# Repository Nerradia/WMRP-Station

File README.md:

# WMRP-Station

Seeing the quality of WMRP tips from Weller, I wanted to buil my own station, cheaper that the official one.
It is still in development and some improvements are still to be made.
There is two PCBs : The first one seats in the base, and the other one is in the handle.

The first circuit has two microcontrollers, one dedicated to power regulation, and the other one for everything else. The power regulation is made with a half-bridge filtered with two LC low-pass filters. The PWM frequency is at about 100 KHz (I'm not sure, I need to check that), this way, the heating element will receive a smooth current and voltage. On an early version of this station, which was sending square-waves, it seemed to break the heating element.

The second is just made of some sensors to measure temperature of the tip, measure the acceleration of the handle (for automatic start and stop), to detect touch and finally to light up an RGB LED. These two last functions are not yet implemented, I neeed to make an other PCB.

To order the last version of PCBs :
https://pcbs.io/share/zjX5Z
https://pcbs.io/share/z5bD1

BOM is coming soon.

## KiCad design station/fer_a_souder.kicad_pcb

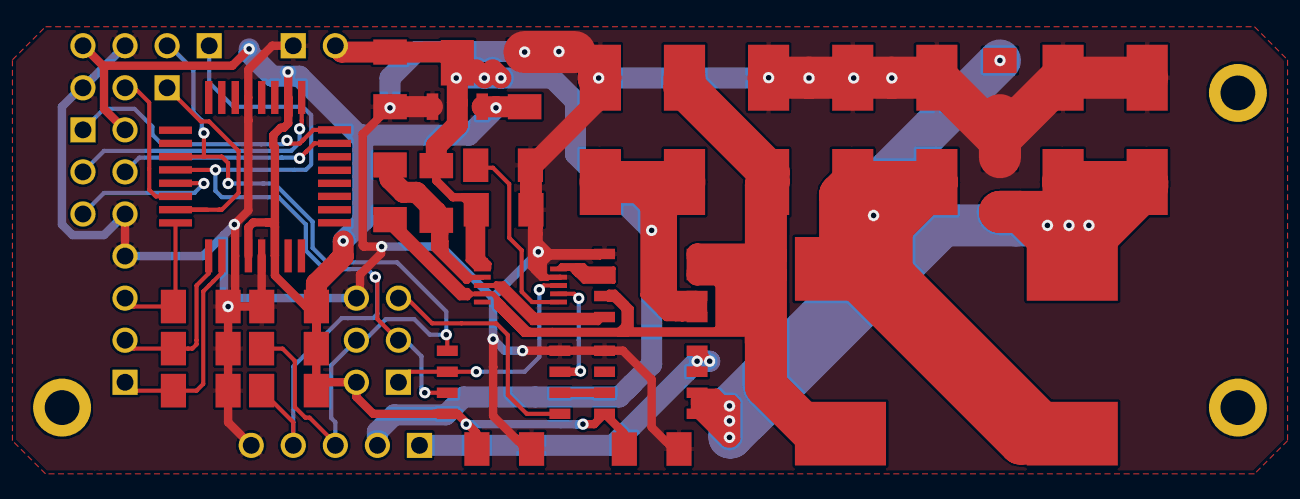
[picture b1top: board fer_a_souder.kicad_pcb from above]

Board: 2 copper layers, 42 parts (0 on the bottom side), 26 nets.

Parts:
C1, C2, C3, C6, C7, C12, C15, C17: 1u; SM1206
C4: CAPAPOL; SMD2917
C5, C8, C16, C18: 100u; SMD2917
C10, C13, C14: 1n; SM1206
C11: 200n; SM1206
CON1, CON2: AVR-ISP-6; pin_array_3x2
D1, D2: DIODESCH; SMD2917
D5: DIODE; SM1206
IC1: ATMEGA328P-A; TQFP32
IC2: ATTINY85-S; SOIC-8
K1: CONN_3; PIN_ARRAY_3X1
L1, L2: 47u; INDCMS12.5
P1: CONN_2; PIN_ARRAY_2X1
P2: CONN_5; PIN_ARRAY_5x1
P3, P4: CONN_4; PIN_ARRAY_4x1
R1: 10k; SM1206
R2, R3: 2.2k; SM1206
TrouFixation2.1mm, TrouFixation2.1mm#2, TrouFixation2.1mm#3: P***; trouFixation3.1mm
U1: 7805; sot89
U2: LM5106; msoic-10
U3: ACS712; so-8
U5: FDS6898A; so-8
svg2mod-rev: G***; svg2mod-rev

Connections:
+3.3V: C1.1, C3.1, C6.2, C7.1, CON1.2, CON2.2, IC1.4, IC1.6, IC1.18, IC2.8, P3.4, R2.1, R3.1, U1.VO, U3.8
+12V: C2.1, C4.1, C12.1, D1.1, D5.1, P1.2, P2.2, U1.VI, U2.1, U5.5, U5.6
/ISENS: IC2.2, U3.7
/MISO: CON1.1, IC1.16
/MISO2: CON2.1, IC2.6, U2.8
/MOSI: CON1.4, IC1.15
/MOSI2: CON2.4, IC1.27, IC2.5, P2.3, P3.2, R2.2
/RST: CON1.5, IC1.29
/RST_2: CON2.5, IC2.1
/RXD: IC1.30, K1.2
/SCK: CON1.3, IC1.17
/SCK_2: CON2.3, IC1.28, IC2.7, P2.4, P3.1, R3.2
/TXD: IC1.31, K1.1
/p: C10.1, IC1.2, P4.1
/pont_en: IC2.3, U2.7
/r+: C14.1, IC1.32, P4.3
/r-: C13.1, IC1.1, P4.2
/resistance: P2.1, U3.3, U3.4
GND: C1.2, C2.2, C3.2, C4.2, C5.2, C6.1, C7.2, C8.2, C10.2, C12.2, C13.2, C14.2, C15.2, C16.2, C17.2, C18.2, CON1.6, CON2.6, D2.2, IC1.3, IC1.5, IC1.21, IC2.4, K1.3, P1.1, P2.5, P3.3, P4.4, R1.2, U1.GND, U2.9, U3.5, U5.1
unnamed: C11.1, D5.2, U2.2
unnamed: R1.1, U2.6
unnamed: U2.3, U5.4
unnamed: U2.10, U5.2
unnamed: C11.2, D1.2, D2.1, L1.1, U2.4, U5.3, U5.7, U5.8
unnamed: C8.1, C17.1, C18.1, L2.2, U3.1, U3.2
unnamed: C5.1, C15.1, C16.1, L1.2, L2.1

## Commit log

2017-11-15 Initial commit
    There's a bad component in cache (the power MOSFET)
2017-11-15 Initial commit, I have to check it
2017-11-16 Swapped folders
2017-11-16 Initial commit, very ugly software !
